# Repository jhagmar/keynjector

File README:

ABOUT THE PROJECT

There are several bad solutions to managing passwords securely, e.g.,

1) Having the same (easy to guess) password for every account
2) Keeping your passwords on a Post-It under your keyboard
3) Using a password manager on your computer

You might be surprised that item 3 made the list, but password managers keep all passwords in a file encrypted with a master password. When the user retrieves a password, all other passwords are decrypted and exposed in RAM, in an environment with dozens of other, potentially malicious, processes with internet access. Password managing software often use secure memory to increase security. However, a keylogger can be used to record the master password, and then we are back at the original problem.

The keynjector project tries to raise the bar by providing the password file decryption in a dedicated device, connected to the host with a USB cable. The password file, encrypted with OpenPGP symmetric encryption, is provided on a microSD card that the user inserts into the device. When the user requests a password, the device emulates a USB keyboard, and types the password on the host computer.

This solution offers a more secure solution compared to a traditional password manager:
1) There are no other processes running on the device that could potentially steal the information.
2) The USB keyboard interface is one-directional. There is no possibility for the host to inject code into the keynjector device.
3) The master password file can be easily removed and destroyed, e.g., by burning the microSD card, if needed.
4) The device can be used on any computer that recognizes a USB keyboard, without any loss of security.

The keynjector project consists of several sub-projects for the PCB layout, the firmware, the case for the device, etc. See below for a brief overview of the project directory structure.

GENERAL INFORMATION

Unless otherwise stated, all files in the keynjector project are Copyright Jonas Hagmar 2014, and licensed under GPL v2. A copy of the GPL v2 can be found in LICENSE.

Please refer to the AUTHORS file for contact information. 

DIRECTORY STRUCTURE

A brief overview of the directory structure of the project:

cad - CAD drawings

cad/case - OpenSCAD drawing of the case, suitable for 3D printing.

docs - documents

docs/datasheets - datasheets of components listed in the bill of materials (BOM)

hw - hardware designs

hw/bom - BOM for the hardware designs

hw/keynjector - KiCad project for the keynjector PCB

hw/zifbrkout - KiCad project for a breakout board which is helpful for testing the LCD connector on the keynjector board

misc - miscellaneous

misc/fonts - fonts used in the keynjector software

sw - software

sw/keynjector - Atmel Studio ASF project for the keynjector firmware

sw/keynjector_ui - Visual Studio 2010 project for desktop development of the keynjector UI, for faster iterations than trying out the code directly on the keynjector board

THIRD PARTY LICENSES

The project uses the following third party software:

Atmel ASF

/* Copyright (c) 2009-2014 Atmel Corporation. All rights reserved.
 *
 * \asf_license_start
 *
 * \page License
 *
 * Redistribution and use in source and binary forms, with or without
 * modification, are permitted provided that the following conditions are met:
 *
 * 1. Redistributions of source code must retain the above copyright notice,
 *    this list of conditions and the following disclaimer.
 *
 * 2. Redistributions in binary form must reproduce the above copyright notice,
 *    this list of conditions and the following disclaimer in the documentation
 *    and/or other materials provided with the distribution.
 *
 * 3. The name of Atmel may not be used to endorse or promote products derived
 *    from this software without specific prior written permission.
 *
 * 4. This software may only be redistributed and used in connection with an
 *    Atmel microcontroller product.
 *
 * THIS SOFTWARE IS PROVIDED BY ATMEL "AS IS" AND ANY EXPRESS OR IMPLIED
 * WARRANTIES, INCLUDING, BUT NOT LIMITED TO, THE IMPLIED WARRANTIES OF
 * MERCHANTABILITY, FITNESS FOR A PARTICULAR PURPOSE AND NON-INFRINGEMENT ARE
 * EXPRESSLY AND SPECIFICALLY DISCLAIMED. IN NO EVENT SHALL ATMEL BE LIABLE FOR
 * ANY DIRECT, INDIRECT, INCIDENTAL, SPECIAL, EXEMPLARY, OR CONSEQUENTIAL
 * DAMAGES (INCLUDING, BUT NOT LIMITED TO, PROCUREMENT OF SUBSTITUTE GOODS
 * OR SERVICES; LOSS OF USE, DATA, OR PROFITS; OR BUSINESS INTERRUPTION)
 * HOWEVER CAUSED AND ON ANY THEORY OF LIABILITY, WHETHER IN CONTRACT,
 * STRICT LIABILITY, OR TORT (INCLUDING NEGLIGENCE OR OTHERWISE) ARISING IN
 * ANY WAY OUT OF THE USE OF THIS SOFTWARE, EVEN IF ADVISED OF THE
 * POSSIBILITY OF SUCH DAMAGE.
 *
 * \asf_license_stop
 *
 */

CMSIS

* -------------------------------------------------------------------
* Copyright (C) 2011 ARM Limited. All rights reserved.  
* 
* Date:        11 October 2011  
* Revision:    V3.00 
*  
* Project:     Cortex Microcontroller Software Interface Standard (CMSIS)
* Title:       Release Note for CMSIS
*
* -------------------------------------------------------------------

NOTE - Open the index.html file to access CMSIS documentation

The Cortex Microcontroller Software Interface Standard (CMSIS) provides a single standard across all 
Cortex-Mx processor series vendors. It enables code re-use and code sharing across software projects 
and reduces time-to-market for new embedded applications.

CMSIS is released under the terms of the end user license agreement ("CMSIS END USER LICENCE AGREEMENT.pdf").
Any user of the software package is bound to the terms and conditions of the end user license agreement.

FatFS

 FatFs module is an open source software to implement FAT file system to
 small embedded systems. This is a free software and is opened for education,
 research and commercial developments under license policy of following trems.

  Copyright (C) 2011, ChaN, all right reserved.

 * The FatFs module is a free software and there is NO WARRANTY.
 * No restriction on use. You can use, modify and redistribute it for
   personal, non-profit or commercial product UNDER YOUR RESPONSIBILITY.
 * Redistributions of source code must retain the above copyright notice.

miniz

miniz is public domain and has the following license:

/*
  This is free and unencumbered software released into the public domain.

  Anyone is free to copy, modify, publish, use, compile, sell, or
  distribute this software, either in source code form or as a compiled
  binary, for any purpose, commercial or non-commercial, and by any
  means.

  In jurisdictions that recognize copyright laws, the author or authors
  of this software dedicate any and all copyright interest in the
  software to the public domain. We make this dedication for the benefit
  of the public at large and to the detriment of our heirs and
  successors. We intend this dedication to be an overt act of
  relinquishment in perpetuity of all present and future rights to this
  software under copyright law.

  THE SOFTWARE IS PROVIDED "AS IS", WITHOUT WARRANTY OF ANY KIND,
  EXPRESS OR IMPLIED, INCLUDING BUT NOT LIMITED TO THE WARRANTIES OF
  MERCHANTABILITY, FITNESS FOR A PARTICULAR PURPOSE AND NONINFRINGEMENT.
  IN NO EVENT SHALL THE AUTHORS BE LIABLE FOR ANY CLAIM, DAMAGES OR
  OTHER LIABILITY, WHETHER IN AN ACTION OF CONTRACT, TORT OR OTHERWISE,
  ARISING FROM, OUT OF OR IN CONNECTION WITH THE SOFTWARE OR THE USE OR
  OTHER DEALINGS IN THE SOFTWARE.

  For more information, please refer to <http://unlicense.org/>
*/

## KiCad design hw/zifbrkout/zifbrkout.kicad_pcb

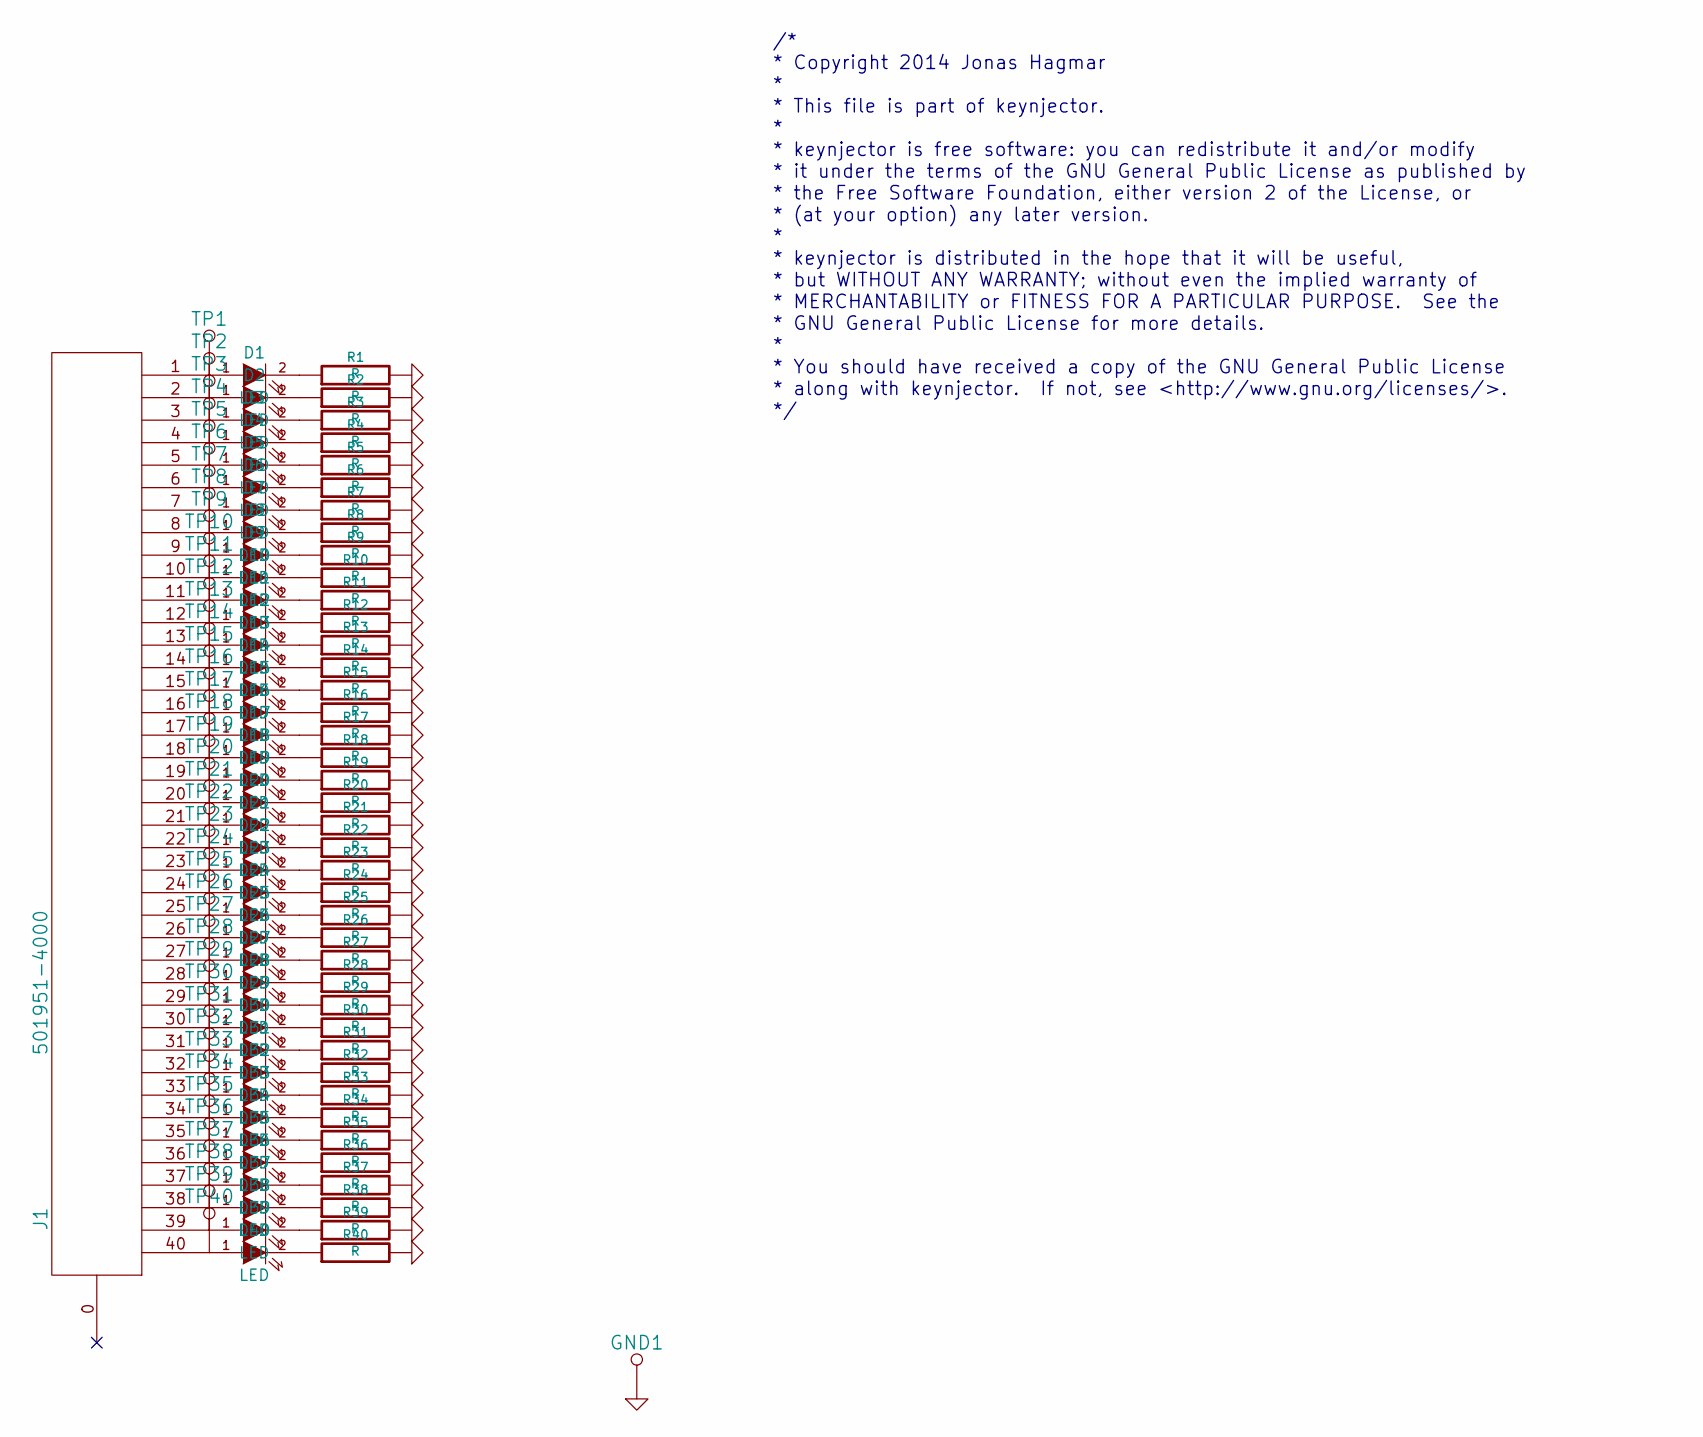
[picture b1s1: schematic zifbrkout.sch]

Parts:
D1, D2, D3, D4, D5, D6, D7, D8, D9, D10, D11, D12, D13, D14, D15, D16, D17, D18, D19, D20, D21, D22, D23, D24, D25, D26, D27, D28, D29, D30, D31, D32, D33, D34, D35, D36, D37, D38, D39, D40: LED
GND1: EXTGND
J1: 501951-4000
R1, R2, R3, R4, R5, R6, R7, R8, R9, R10, R11, R12, R13, R14, R15, R16, R17, R18, R19, R20, R21, R22, R23, R24, R25, R26, R27, R28, R29, R30, R31, R32, R33, R34, R35, R36, R37, R38, R39, R40: R
TP1, TP2, TP3, TP4, TP5, TP6, TP7, TP8, TP9, TP10, TP11, TP12, TP13, TP14, TP15, TP16, TP17, TP18, TP19, TP20, TP21, TP22, TP23, TP24, TP25, TP26, TP27, TP28, TP29, TP30, TP31, TP32, TP33, TP34, TP35, TP36, TP37, TP38, TP39, TP40: TP

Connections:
GND: GND1.1, R1.2, R2.2, R3.2, R4.2, R5.2, R6.2, R7.2, R8.2, R9.2, R10.2, R11.2, R12.2, R13.2, R14.2, R15.2, R16.2, R17.2, R18.2, R19.2, R20.2, R21.2, R22.2, R23.2, R24.2, R25.2, R26.2, R27.2, R28.2, R29.2, R30.2, R31.2, R32.2, R33.2, R34.2, R35.2, R36.2, R37.2, R38.2, R39.2, R40.2
unnamed: D26.2 (K), R26.1
unnamed: D31.2 (K), R31.1
unnamed: D30.2 (K), R30.1
unnamed: D29.2 (K), R29.1
unnamed: D28.2 (K), R28.1
unnamed: D27.2 (K), R27.1
unnamed: D25.2 (K), R25.1
unnamed: D24.2 (K), R24.1
unnamed: D23.2 (K), R23.1
unnamed: D22.2 (K), R22.1
unnamed: D40.2 (K), R40.1
unnamed: D39.2 (K), R39.1
unnamed: D38.2 (K), R38.1
unnamed: D37.2 (K), R37.1
unnamed: D36.2 (K), R36.1
unnamed: D35.2 (K), R35.1
unnamed: D34.2 (K), R34.1
unnamed: D33.2 (K), R33.1
unnamed: D32.2 (K), R32.1
unnamed: D11.1 (A), J1.11, TP11.1
unnamed: D24.1 (A), J1.24, TP24.1
unnamed: D14.1 (A), J1.14, TP14.1
unnamed: D33.1 (A), J1.33, TP33.1
unnamed: D23.1 (A), J1.23, TP23.1
unnamed: D13.1 (A), J1.13, TP13.1
unnamed: D32.1 (A), J1.32, TP32.1
unnamed: D22.1 (A), J1.22, TP22.1
unnamed: D12.1 (A), J1.12, TP12.1
unnamed: D31.1 (A), J1.31, TP31.1
unnamed: D21.1 (A), J1.21, TP21.1
unnamed: D34.1 (A), J1.34, TP34.1
unnamed: D40.1 (A), J1.40, TP40.1
unnamed: D30.1 (A), J1.30, TP30.1
unnamed: D20.1 (A), J1.20, TP20.1
unnamed: D10.1 (A), J1.10, TP10.1
unnamed: D9.1 (A), J1.9, TP9.1
unnamed: D8.1 (A), J1.8, TP8.1
unnamed: D7.1 (A), J1.7, TP7.1
unnamed: D6.1 (A), J1.6, TP6.1
unnamed: D5.1 (A), J1.5, TP5.1
unnamed: D18.1 (A), J1.18, TP18.1
unnamed: D39.1 (A), J1.39, TP39.1
unnamed: D29.1 (A), J1.29, TP29.1
unnamed: D19.1 (A), J1.19, TP19.1
unnamed: D38.1 (A), J1.38, TP38.1
unnamed: D28.1 (A), J1.28, TP28.1
unnamed: D4.1 (A), J1.4, TP4.1
unnamed: D37.1 (A), J1.37, TP37.1
unnamed: D27.1 (A), J1.27, TP27.1
unnamed: D17.1 (A), J1.17, TP17.1
unnamed: D36.1 (A), J1.36, TP36.1
unnamed: D26.1 (A), J1.26, TP26.1
unnamed: D16.1 (A), J1.16, TP16.1
unnamed: D35.1 (A), J1.35, TP35.1
unnamed: D25.1 (A), J1.25, TP25.1
unnamed: D15.1 (A), J1.15, TP15.1
unnamed: D3.1 (A), J1.3, TP3.1
unnamed: D2.1 (A), J1.2, TP2.1
unnamed: D1.1 (A), J1.1, TP1.1
unnamed: D21.2 (K), R21.1
unnamed: D8.2 (K), R8.1
unnamed: D7.2 (K), R7.1
unnamed: D6.2 (K), R6.1
unnamed: D5.2 (K), R5.1
unnamed: D4.2 (K), R4.1
unnamed: D9.2 (K), R9.1
unnamed: D3.2 (K), R3.1
unnamed: D2.2 (K), R2.1
unnamed: D14.2 (K), R14.1
unnamed: D18.2 (K), R18.1
unnamed: D17.2 (K), R17.1
unnamed: D16.2 (K), R16.1
unnamed: D15.2 (K), R15.1
unnamed: D13.2 (K), R13.1
unnamed: D12.2 (K), R12.1
unnamed: D11.2 (K), R11.1
unnamed: D10.2 (K), R10.1
unnamed: D1.2 (K), R1.1
unnamed: D19.2 (K), R19.1
unnamed: D20.2 (K), R20.1

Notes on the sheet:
/* * Copyright 2014 Jonas Hagmar * * This file is part of keynjector. * * keynjector is free software: you can redistribute it and/or modify * it under the terms of the GNU General Public License as published by * the Free Software Foundation, either version 2 of the License, or * (at your option) 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

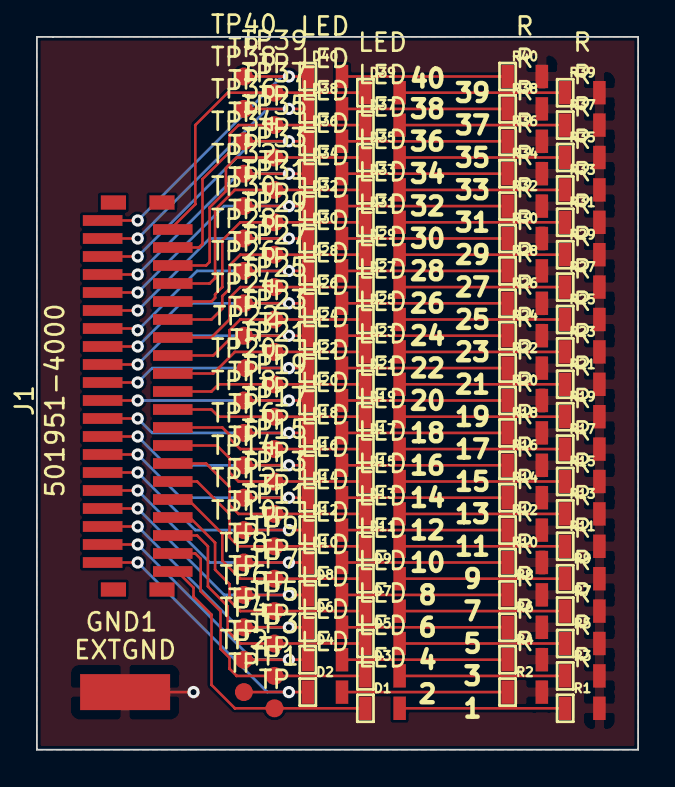
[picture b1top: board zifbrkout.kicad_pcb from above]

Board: 2 copper layers, 33.4 x 39.6 mm, 122 parts (0 on the bottom side), 81 nets.

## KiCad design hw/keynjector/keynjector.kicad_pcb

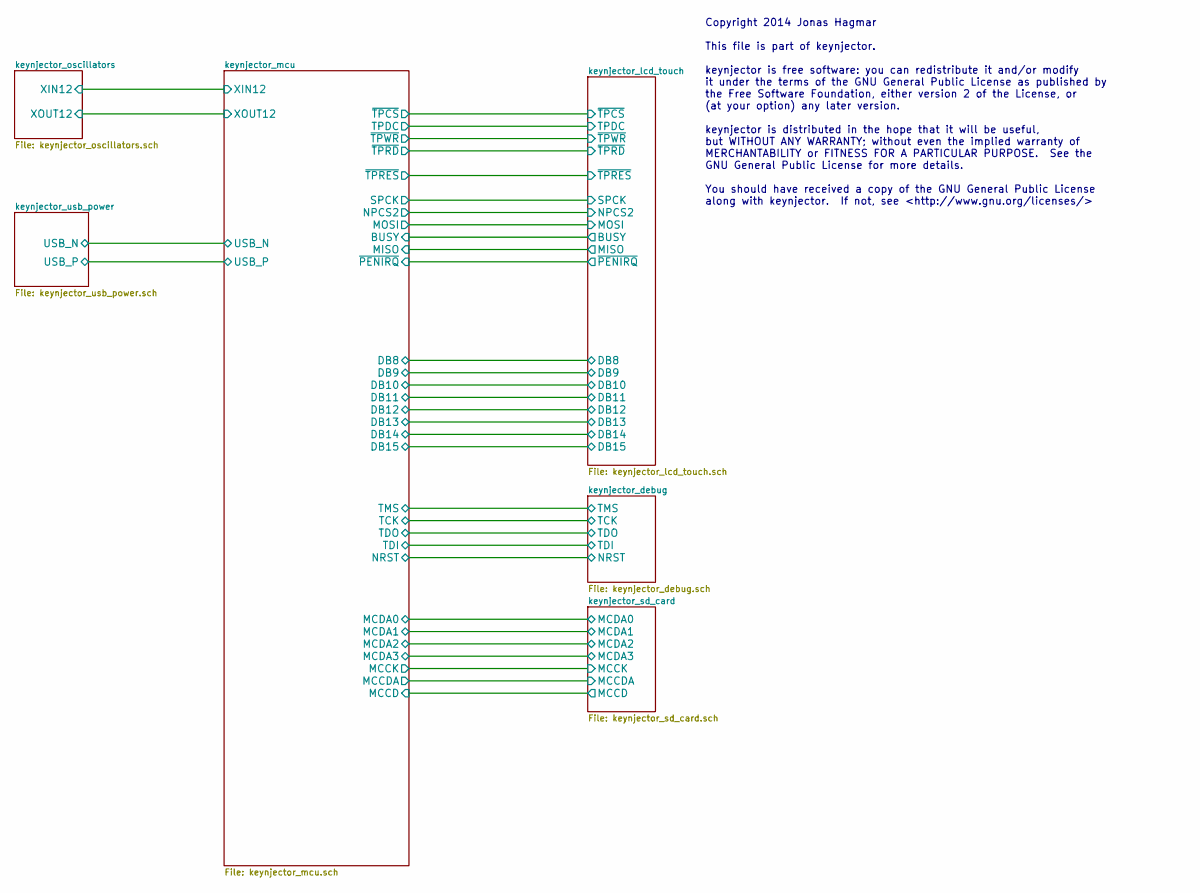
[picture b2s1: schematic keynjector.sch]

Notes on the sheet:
Copyright 2014 Jonas Hagmar This file is part of keynjector. keynjector is free software: you can redistribute it and/or modify it under the terms of the GNU General Public License as published by the Free Software Foundation, either version 2 of the License, or (at your option) any later version. 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

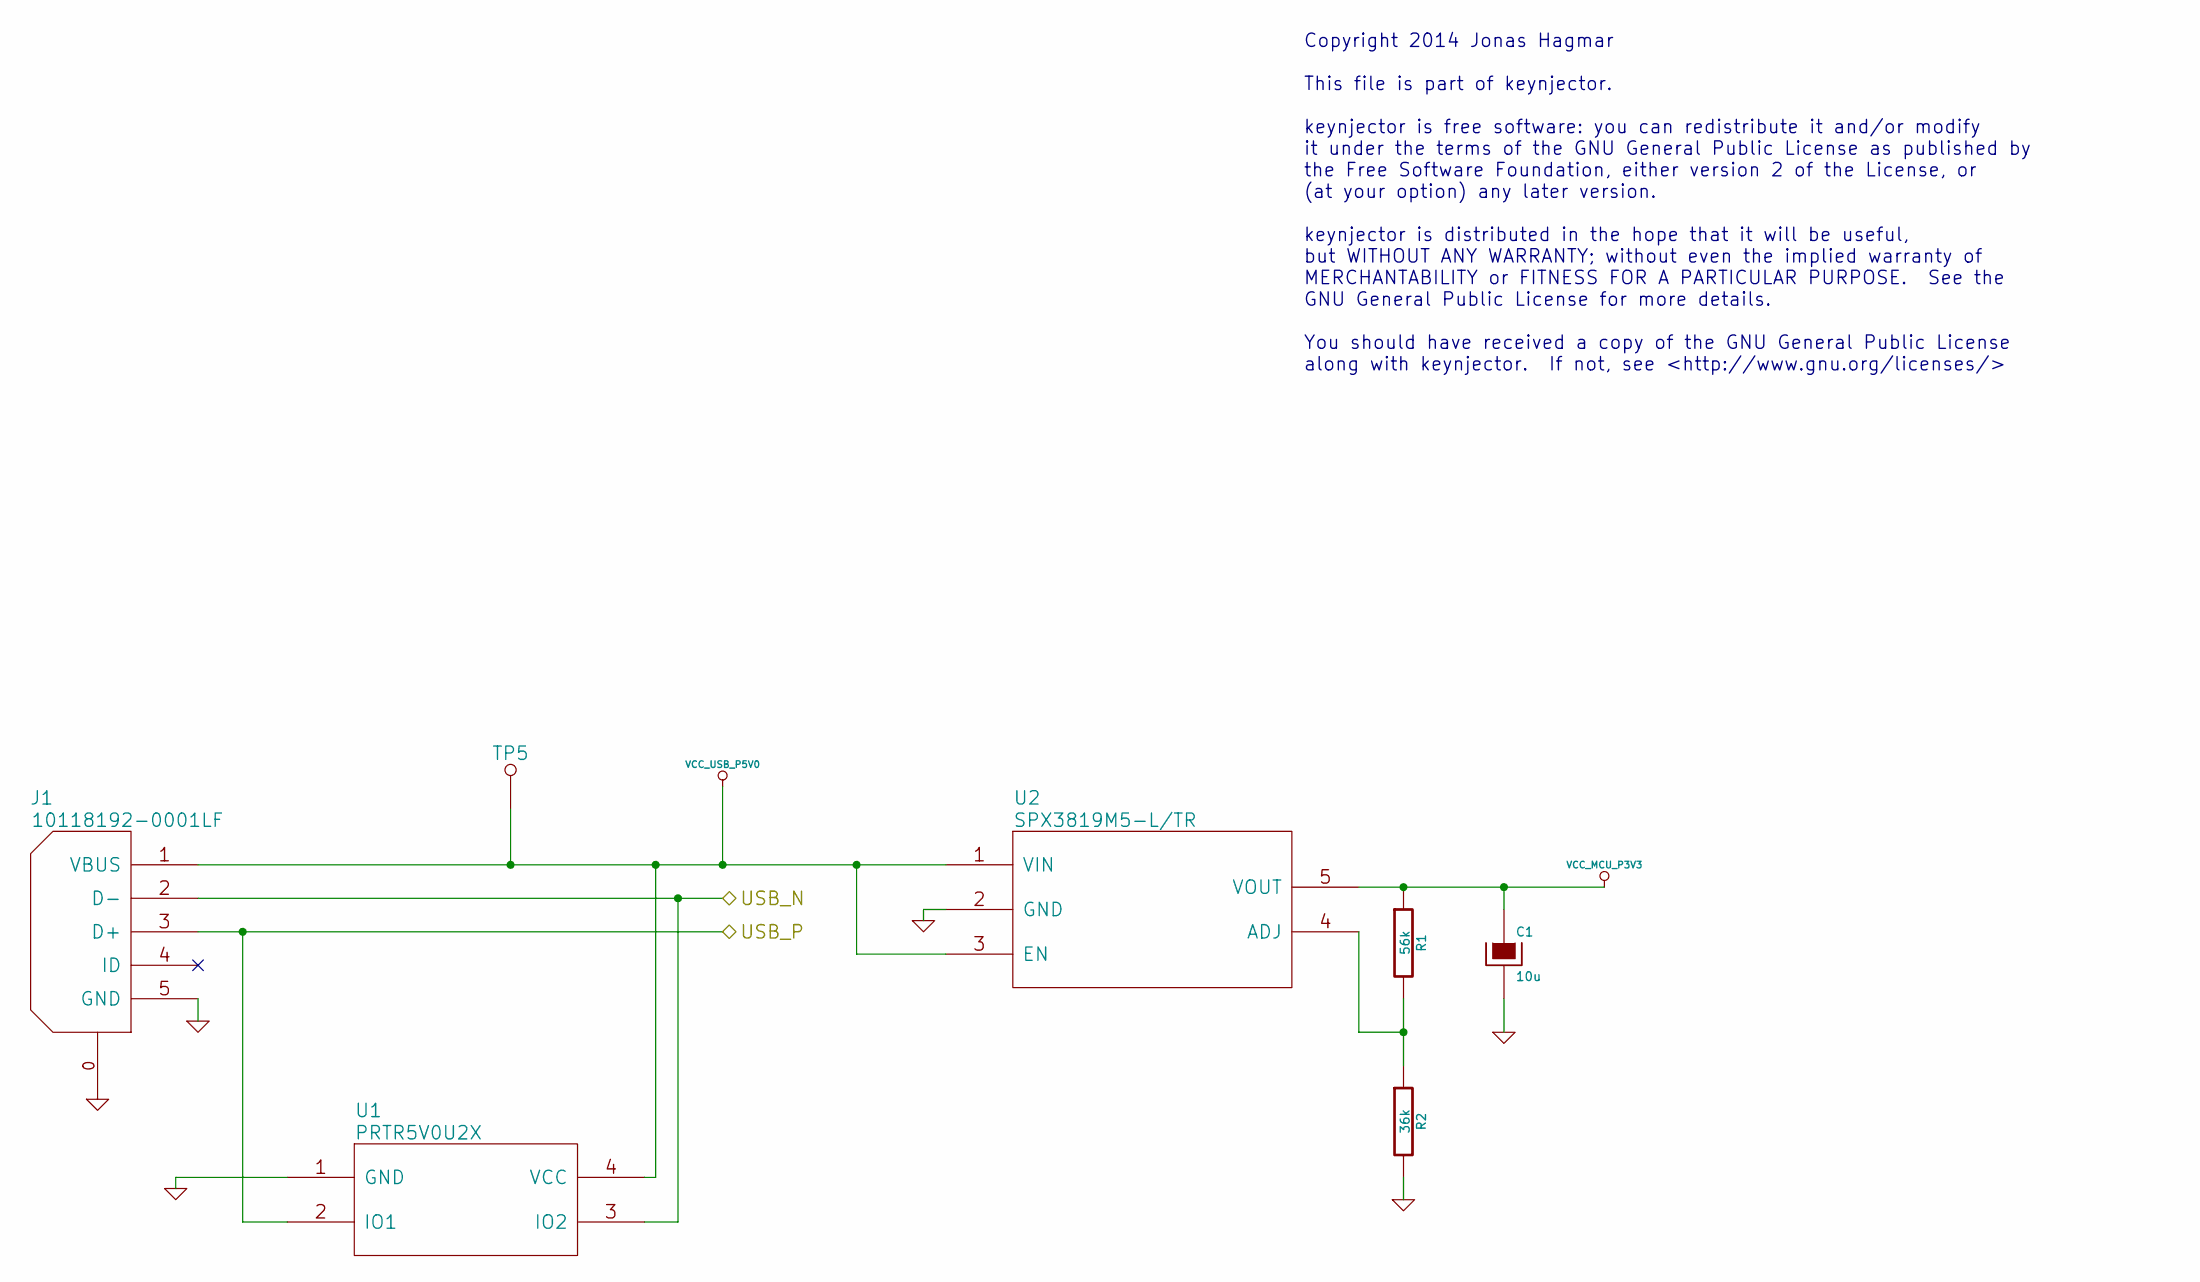
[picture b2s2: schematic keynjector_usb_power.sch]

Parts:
C1: 10u
J1: 10118192-0001LF
R1: 56k
R2: 36k
TP5: TP
U1: PRTR5V0U2X
U2: SPX3819M5-L/TR

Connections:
/keynjector_mcu/USB_N: J1.2 (D-), U1.3 (IO2); also elsewhere on the board
/keynjector_mcu/USB_P: J1.3 (D+), U1.2 (IO1); also elsewhere on the board
GND: C1.2, J1.0, J1.5 (GND), R2.2, U1.1 (GND), U2.2 (GND); also elsewhere on the board
unnamed: R1.2, R2.1, U2.4 (ADJ)
VCC_MCU_P3V3: C1.1, R1.1, U2.5 (VOUT); also elsewhere on the board
VCC_USB_P5V0: J1.1 (VBUS), TP5.1, U1.4 (VCC), U2.1 (VIN), U2.3 (EN)

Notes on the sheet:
Copyright 2014 Jonas Hagmar This file is part of keynjector. keynjector is free software: you can redistribute it and/or modify it under the terms of the GNU General Public License as published by the Free Software Foundation, either version 2 of the License, or (at your option) any later version. 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

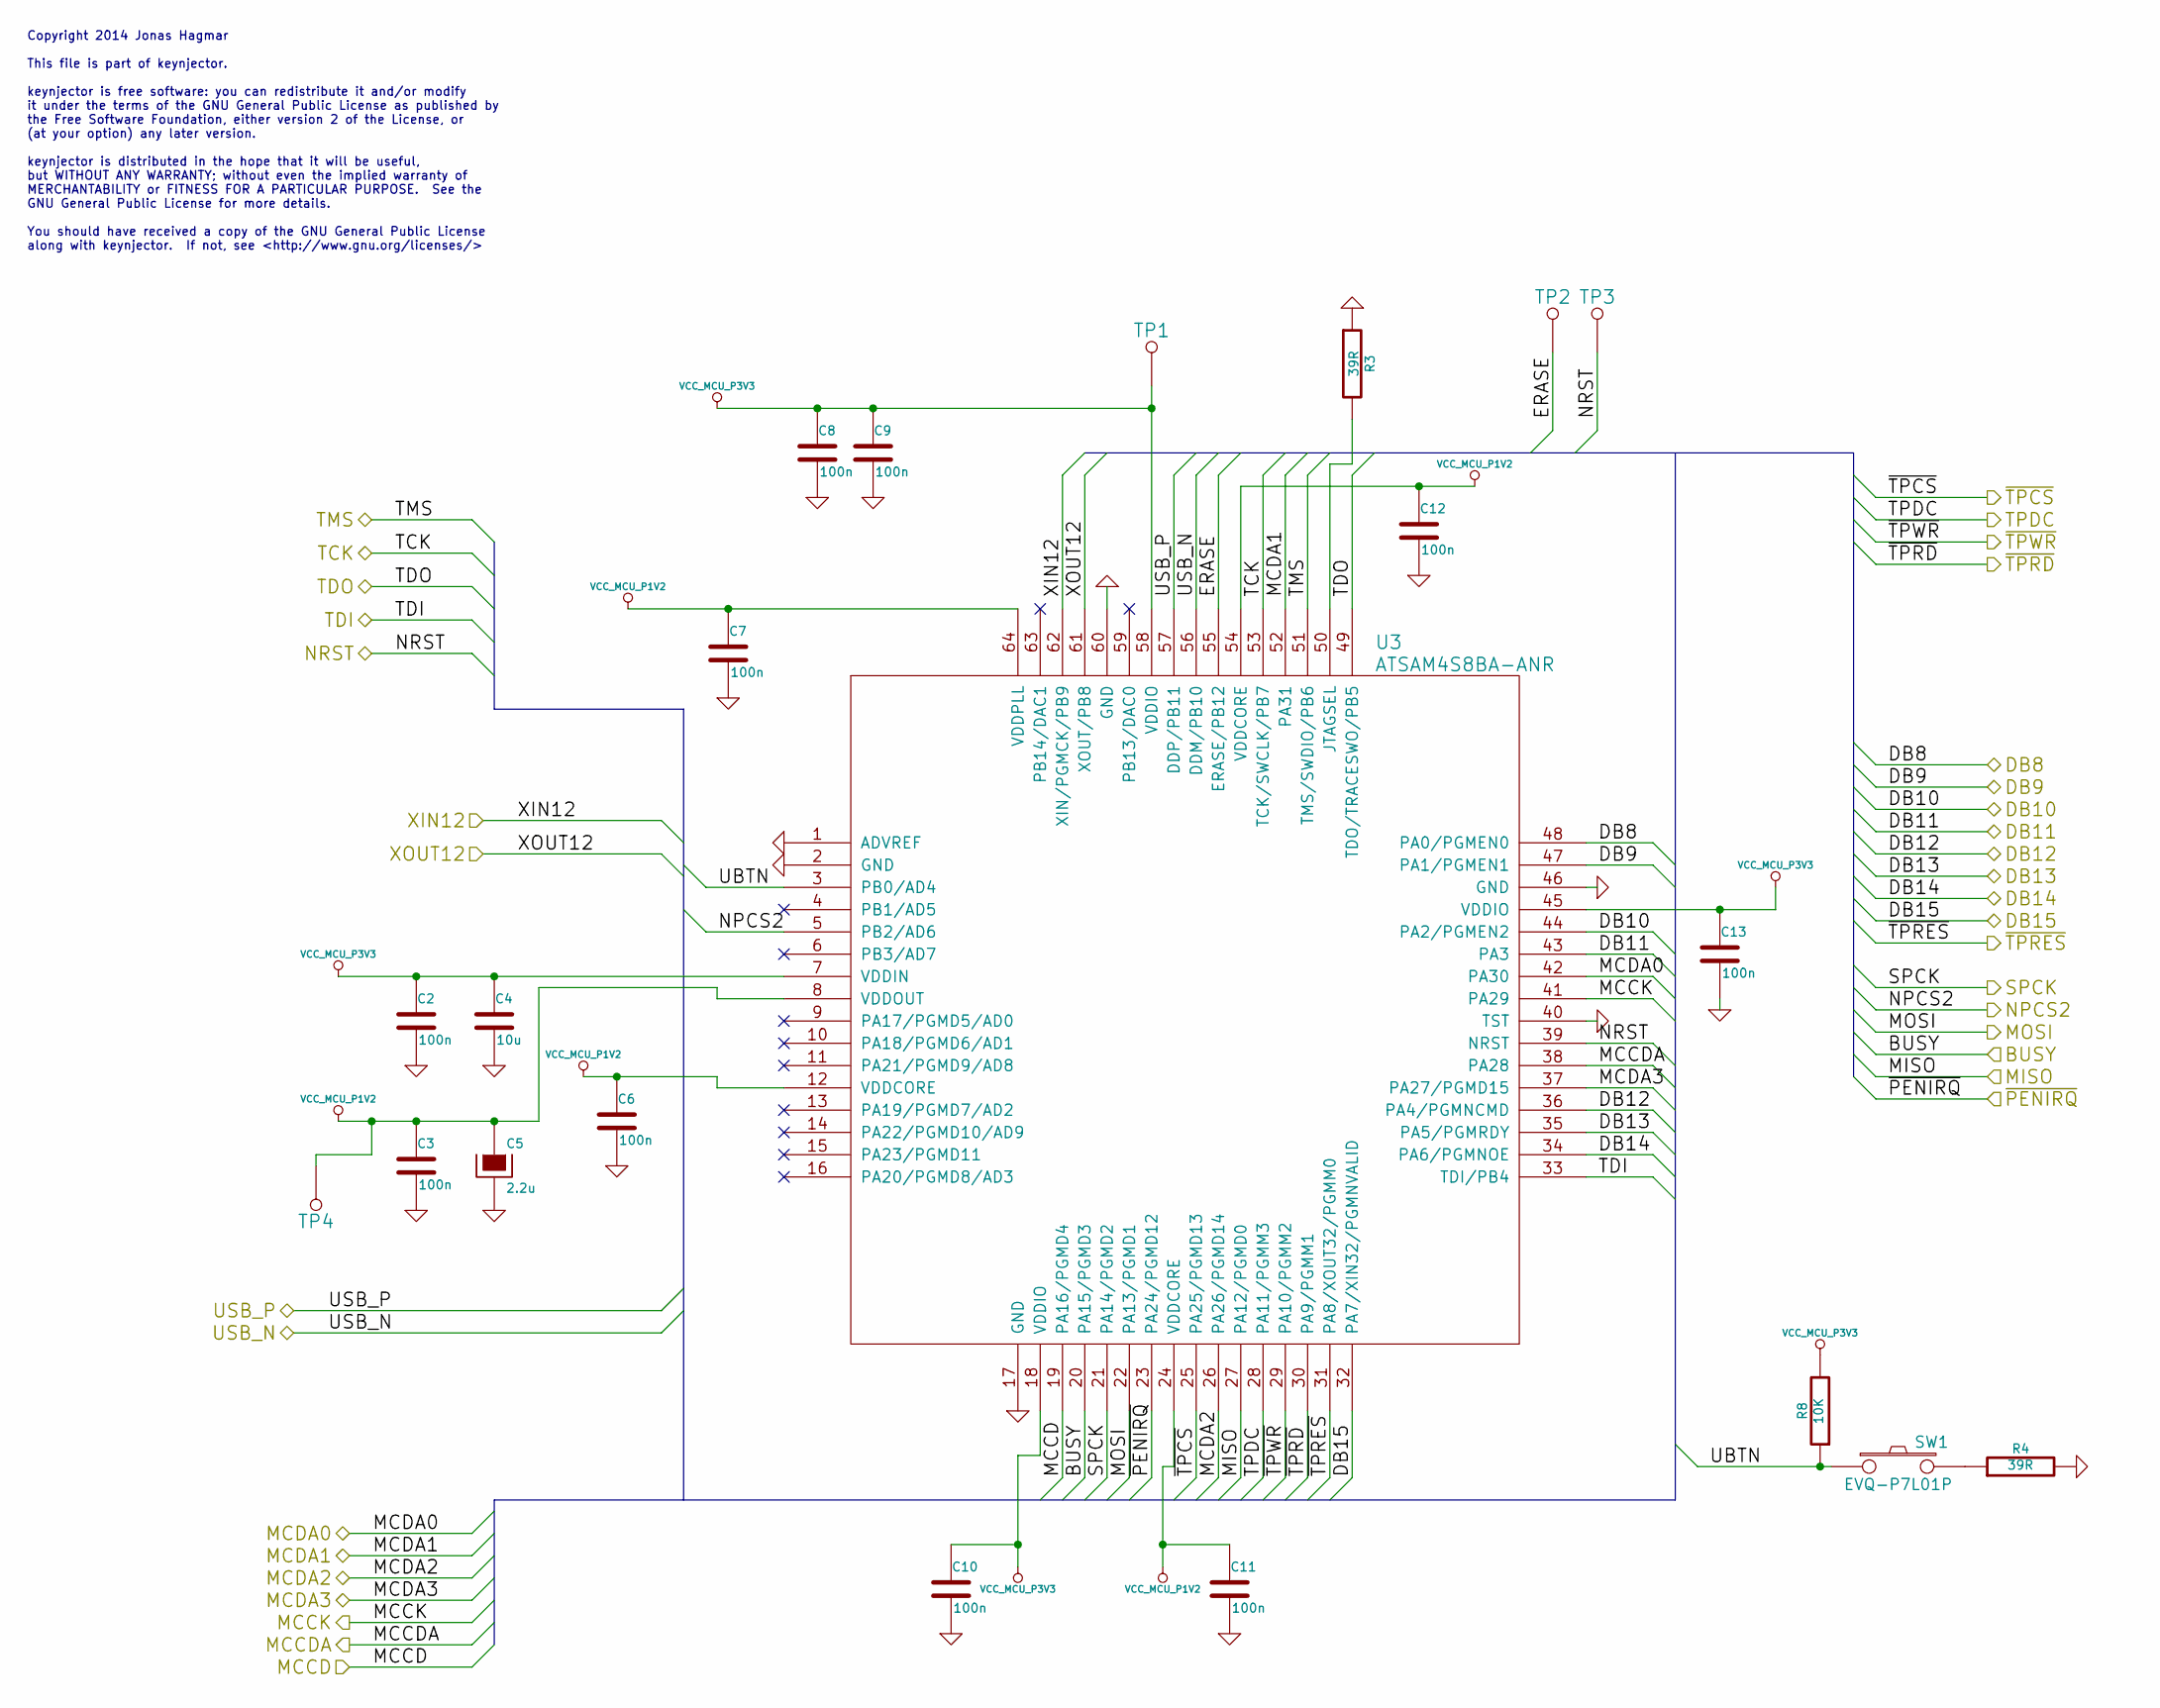
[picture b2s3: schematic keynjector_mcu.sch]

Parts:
C2, C3, C6, C7, C8, C9, C10, C11, C12, C13: 100n
C4: 10u
C5: 2.2u
R3, R4: 39R
R8: 10K
SW1: EVQ-P7L01P
TP1, TP2, TP3, TP4: TP
U3: ATSAM4S8BA-ANR

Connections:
/keynjector_debug/NRST: TP3.1, U3.39 (NRST); also elsewhere on the board
/keynjector_debug/TCK: U3.53 (TCK/SWCLK/PB7); also elsewhere on the board
/keynjector_debug/TDI: U3.33 (TDI/PB4); also elsewhere on the board
/keynjector_debug/TDO: U3.49 (TDO/TRACESWO/PB5); also elsewhere on the board
/keynjector_debug/TMS: U3.51 (TMS/SWDIO/PB6); also elsewhere on the board
/keynjector_lcd_touch/BUSY: U3.20 (PA15/PGMD3); also elsewhere on the board
/keynjector_lcd_touch/DB8: U3.48 (PA0/PGMEN0); also elsewhere on the board
/keynjector_lcd_touch/DB9: U3.47 (PA1/PGMEN1); also elsewhere on the board
/keynjector_lcd_touch/DB10: U3.44 (PA2/PGMEN2); also elsewhere on the board
/keynjector_lcd_touch/DB11: U3.43 (PA3); also elsewhere on the board
/keynjector_lcd_touch/DB12: U3.36 (PA4/PGMNCMD); also elsewhere on the board
/keynjector_lcd_touch/DB13: U3.35 (PA5/PGMRDY); also elsewhere on the board
/keynjector_lcd_touch/DB14: U3.34 (PA6/PGMNOE); also elsewhere on the board
/keynjector_lcd_touch/DB15: U3.32 (PA7/XIN32/PGMNVALID); also elsewhere on the board
/keynjector_lcd_touch/MISO: U3.27 (PA12/PGMD0); also elsewhere on the board
/keynjector_lcd_touch/MOSI: U3.22 (PA13/PGMD1); also elsewhere on the board
/keynjector_lcd_touch/NPCS2: U3.5 (PB2/AD6); also elsewhere on the board
/keynjector_lcd_touch/SPCK: U3.21 (PA14/PGMD2); also elsewhere on the board
/keynjector_lcd_touch/TPDC: U3.28 (PA11/PGMM3); also elsewhere on the board
/keynjector_lcd_touch/~PENIRQ: U3.23 (PA24/PGMD12); also elsewhere on the board
/keynjector_lcd_touch/~TPCS: U3.25 (PA25/PGMD13); also elsewhere on the board
/keynjector_lcd_touch/~TPRD: U3.30 (PA9/PGMM1); also elsewhere on the board
/keynjector_lcd_touch/~TPRES: U3.31 (PA8/XOUT32/PGMM0); also elsewhere on the board
/keynjector_lcd_touch/~TPWR: U3.29 (PA10/PGMM2); also elsewhere on the board
/keynjector_mcu/ERASE: TP2.1, U3.55 (ERASE/PB12)
/keynjector_mcu/MCCD: U3.19 (PA16/PGMD4); also elsewhere on the board
/keynjector_mcu/MCCDA: U3.38 (PA28); also elsewhere on the board
/keynjector_mcu/MCCK: U3.41 (PA29); also elsewhere on the board
/keynjector_mcu/MCDA0: U3.42 (PA30); also elsewhere on the board
/keynjector_mcu/MCDA1: U3.52 (PA31); also elsewhere on the board
/keynjector_mcu/MCDA2: U3.26 (PA26/PGMD14); also elsewhere on the board
/keynjector_mcu/MCDA3: U3.37 (PA27/PGMD15); also elsewhere on the board
/keynjector_mcu/UBTN: R8.1, SW1.1, U3.3 (PB0/AD4)
/keynjector_mcu/USB_N: U3.56 (DDM/PB10); also elsewhere on the board
/keynjector_mcu/USB_P: U3.57 (DDP/PB11); also elsewhere on the board
/keynjector_mcu/XIN12: U3.62 (XIN/PGMCK/PB9); also elsewhere on the board
/keynjector_mcu/XOUT12: U3.61 (XOUT/PB8); also elsewhere on the board
GND: C2.2, C3.2, C4.2, C5.2, C6.2, C7.2, C8.2, C9.2, C10.2, C11.2, C12.2, C13.2, R3.1, R4.2, U3.1 (ADVREF), U3.2 (GND), U3.17 (GND), U3.40 (TST), U3.46 (GND), U3.60 (GND); also elsewhere on the board
unnamed: R3.2, U3.50 (JTAGSEL)
unnamed: R4.1, SW1.2
VCC_MCU_P1V2: C3.1, C5.1, C6.1, C7.1, C11.1, C12.1, TP4.1, U3.8 (VDDOUT), U3.12 (VDDCORE), U3.24 (VDDCORE), U3.54 (VDDCORE), U3.64 (VDDPLL)
VCC_MCU_P3V3: C2.1, C4.1, C8.1, C9.1, C10.1, C13.1, R8.2, TP1.1, U3.7 (VDDIN), U3.18 (VDDIO), U3.45 (VDDIO), U3.58 (VDDIO); also elsewhere on the board

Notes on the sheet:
Copyright 2014 Jonas Hagmar This file is part of keynjector. keynjector is free software: you can redistribute it and/or modify it under the terms of the GNU General Public License as published by the Free Software Foundation, either version 2 of the License, or (at your option) any later version. 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

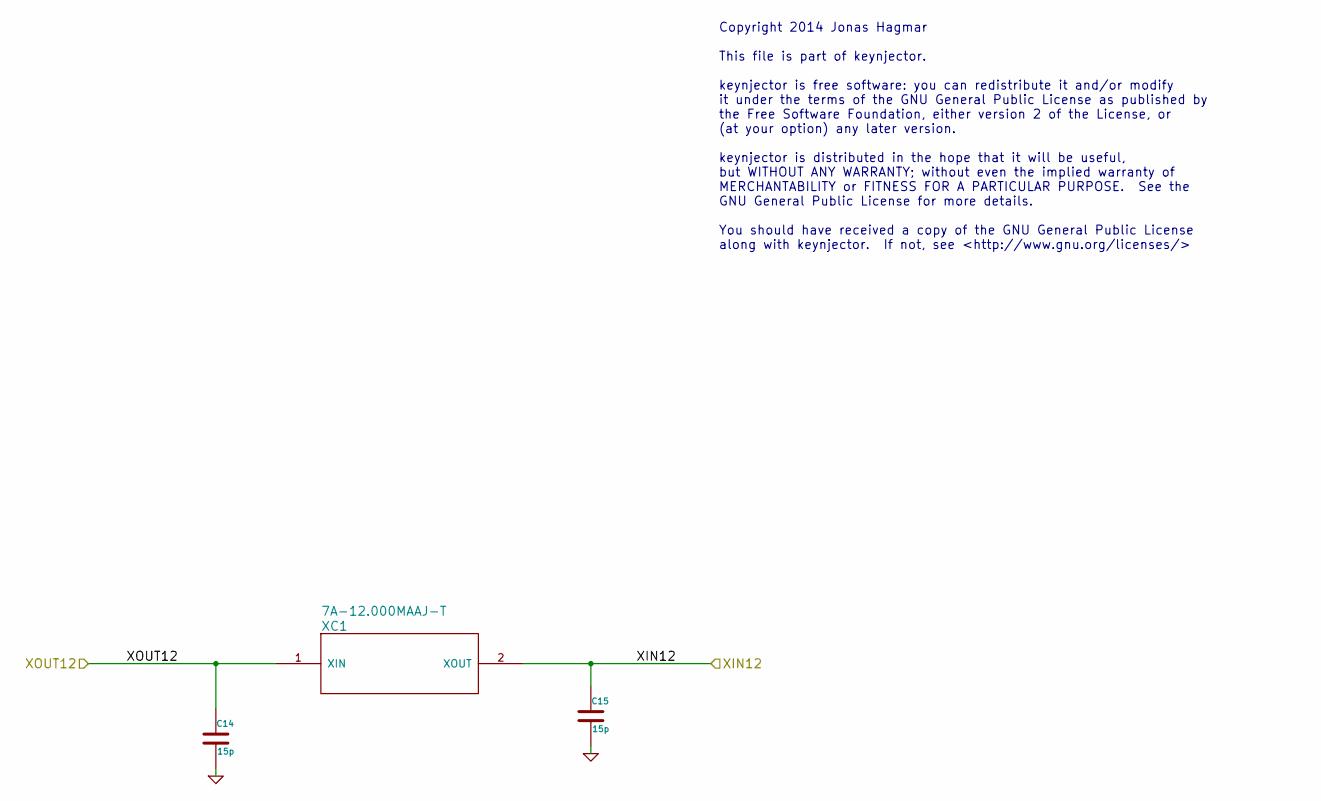
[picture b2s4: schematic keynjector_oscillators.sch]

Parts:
C14, C15: 15p
XC1: 7A-12.000MAAJ-T

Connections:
/keynjector_mcu/XIN12: C15.1, XC1.2 (XOUT); also elsewhere on the board
/keynjector_mcu/XOUT12: C14.1, XC1.1 (XIN); also elsewhere on the board
GND: C14.2, C15.2; also elsewhere on the board

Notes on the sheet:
Copyright 2014 Jonas Hagmar This file is part of keynjector. keynjector is free software: you can redistribute it and/or modify it under the terms of the GNU General Public License as published by the Free Software Foundation, either version 2 of the License, or (at your option) any later version. 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

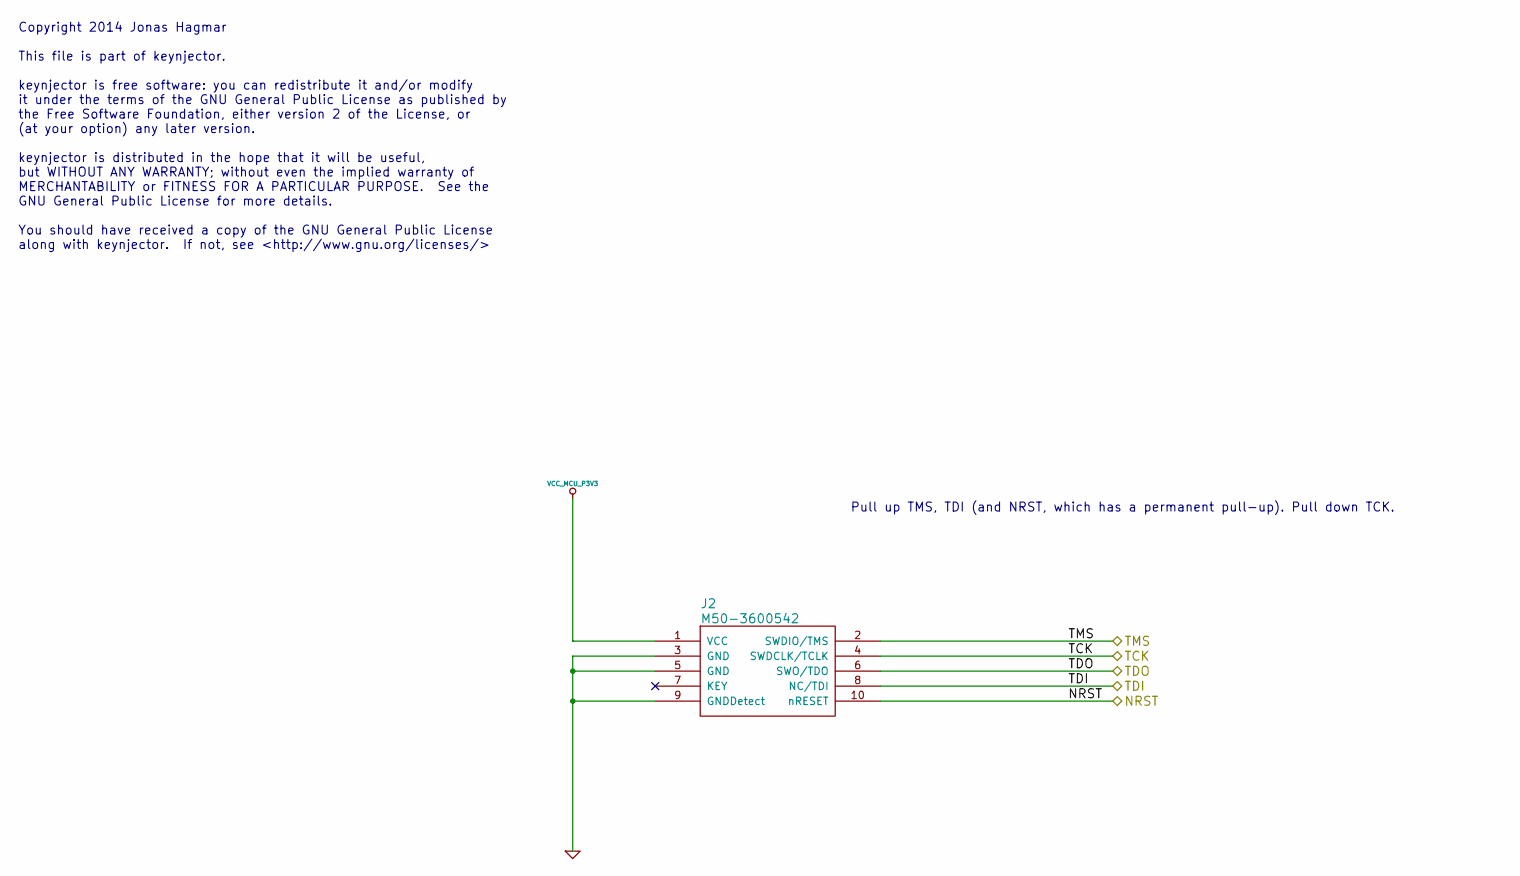
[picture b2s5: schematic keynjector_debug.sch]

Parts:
J2: M50-3600542

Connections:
/keynjector_debug/NRST: J2.10 (nRESET); also elsewhere on the board
/keynjector_debug/TCK: J2.4 (SWDCLK/TCLK); also elsewhere on the board
/keynjector_debug/TDI: J2.8 (NC/TDI); also elsewhere on the board
/keynjector_debug/TDO: J2.6 (SWO/TDO); also elsewhere on the board
/keynjector_debug/TMS: J2.2 (SWDIO/TMS); also elsewhere on the board
GND: J2.3 (GND), J2.5 (GND), J2.9 (GNDDetect); also elsewhere on the board
VCC_MCU_P3V3: J2.1 (VCC); also elsewhere on the board

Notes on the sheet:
Pull up TMS, TDI (and NRST, which has a permanent pull-up). Pull down TCK.
Copyright 2014 Jonas Hagmar This file is part of keynjector. keynjector is free software: you can redistribute it and/or modify it under the terms of the GNU General Public License as published by the Free Software Foundation, either version 2 of the License, or (at your option) any later version. 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

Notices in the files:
hw/keynjector/keynjector.kicad_pcb:
© Jonas Hagmar 2014
